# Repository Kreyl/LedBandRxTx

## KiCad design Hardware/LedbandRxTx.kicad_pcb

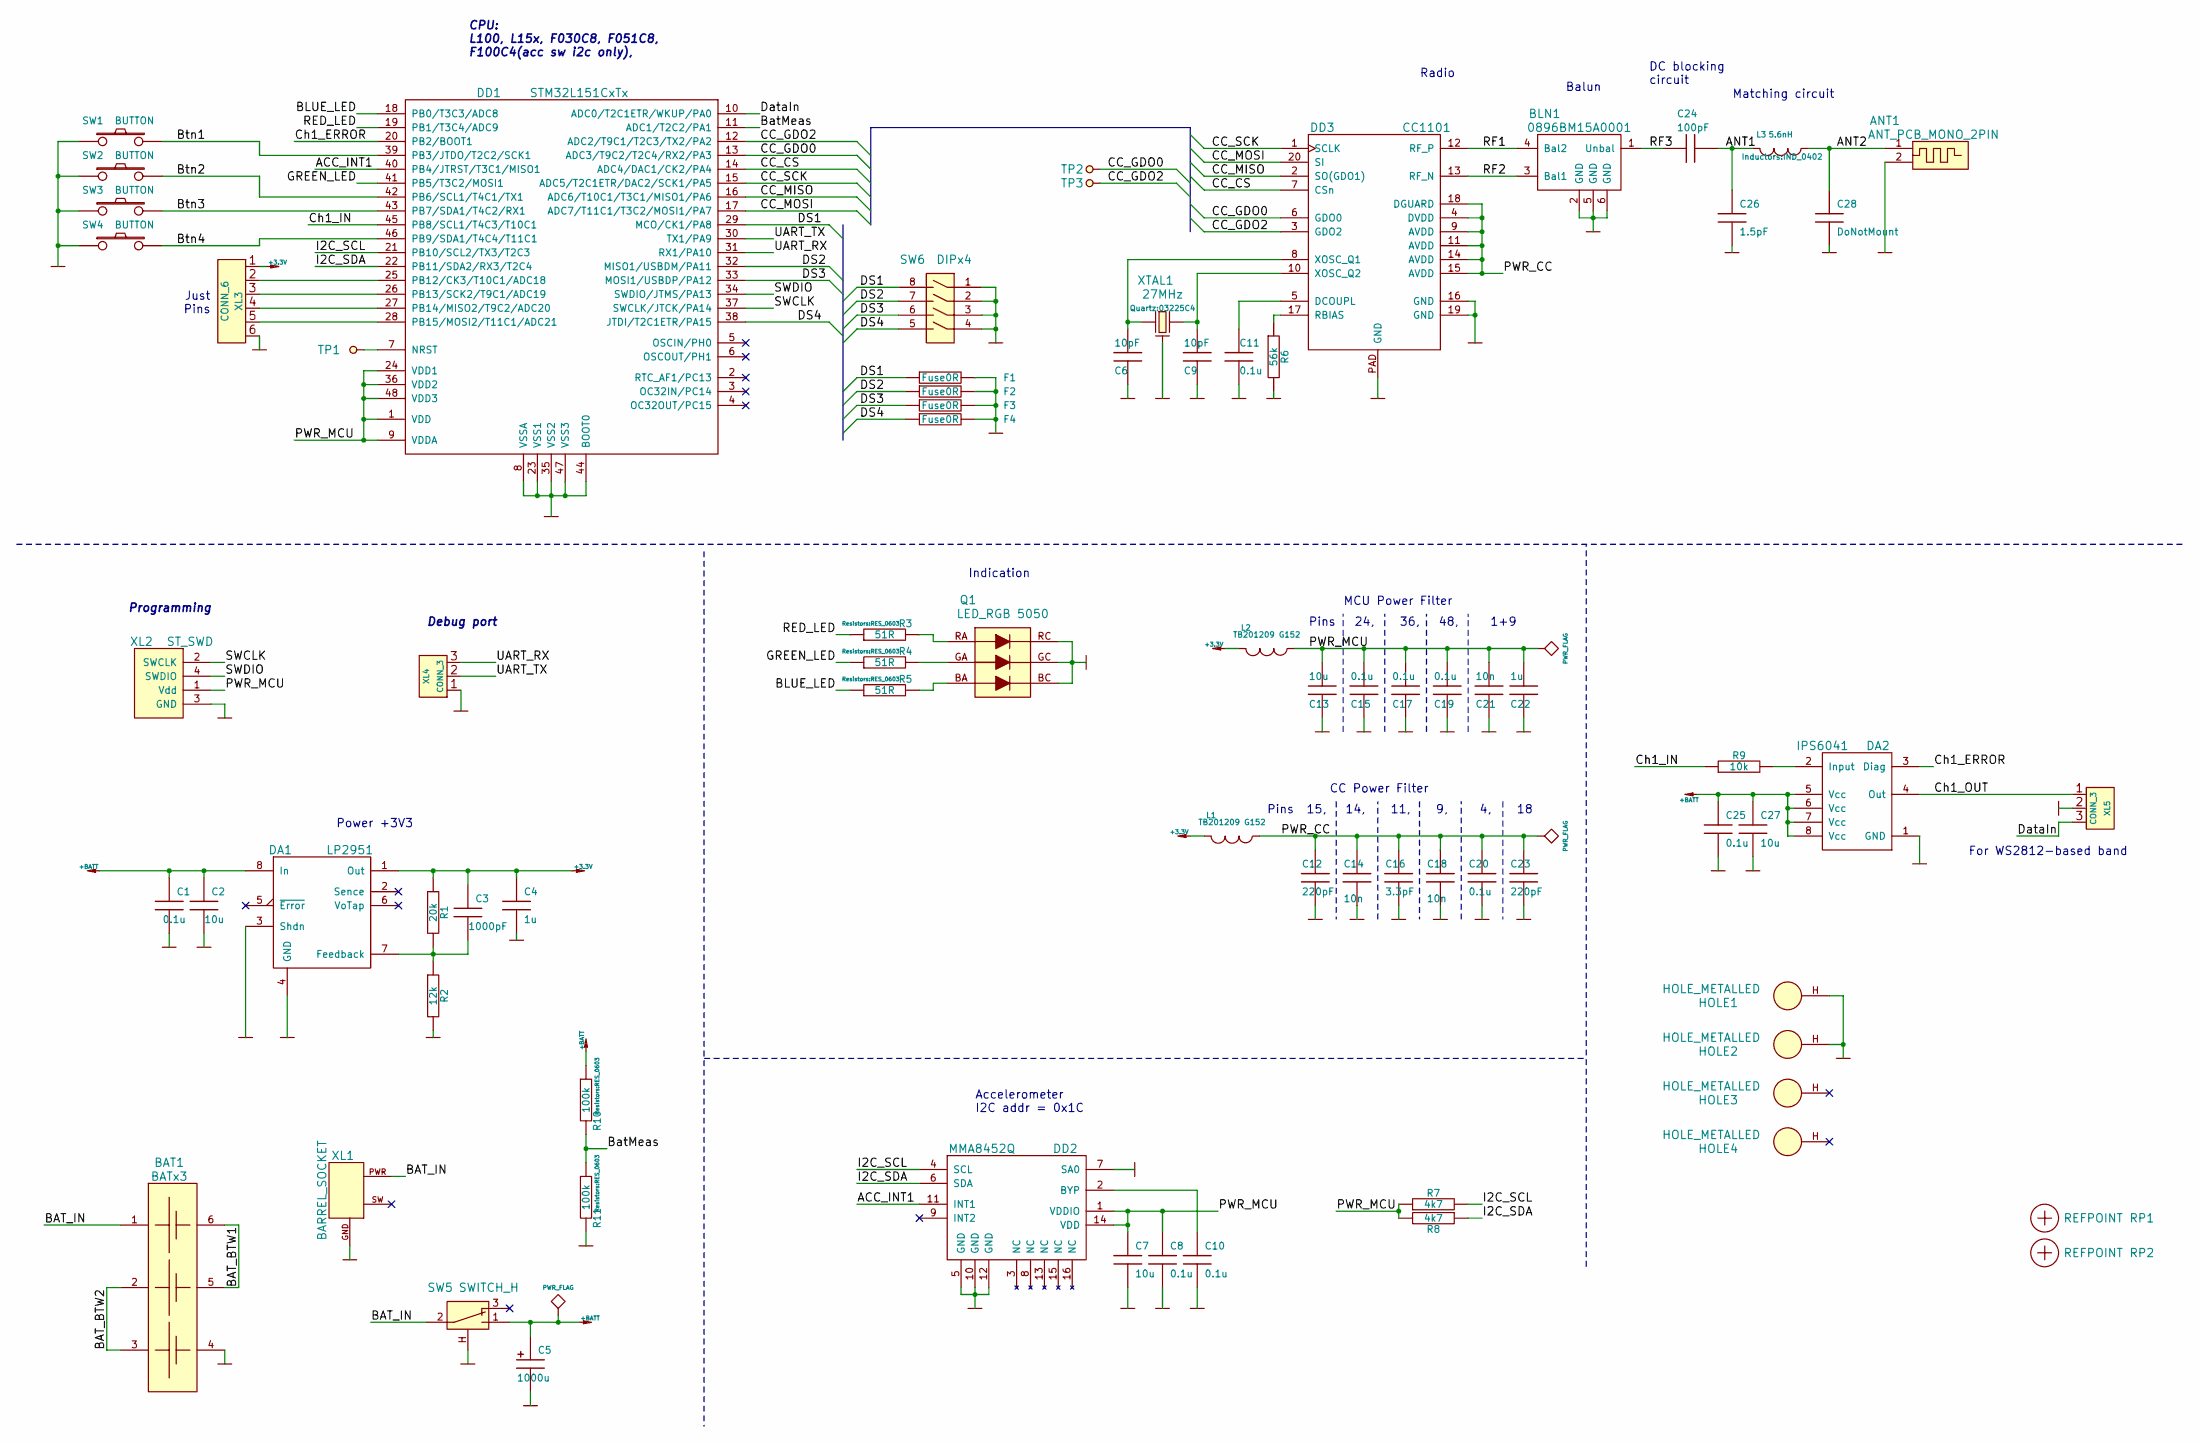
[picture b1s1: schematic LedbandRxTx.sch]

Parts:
ANT1: ANT_PCB_MONO_2PIN; ANT_INVF_LEDBANDRXTX
BAT1: BATx3; 18650x3
BLN1: 0896BM15A0001; BALUN_JOHANSON868
C1, C8, C10, C11, C15, C17, C19, C20, C25: 0.1u; CAP_0603
C2, C7, C13, C27: 10u; CAP_0805
C3: 1000pF; CAP_0603
C4, C22: 1u; CAP_0603
C5: 1000u; CAP_10xxR
C6, C9: 10pF; CAP_0603
C12, C23: 220pF; CAP_0603
C14, C18, C21: 10n; CAP_0603
C16: 3.3pF; CAP_0603
C24: 100pF; CAP_0402
C26: 1.5pF; CAP_0402
C28: DoNotMount; CAP_0402
DA1: LP2951; SO8
DA2: IPS6041; SO8HEATSINK
DD1: STM32L151CxTx; LQFP48
DD2: MMA8452Q; QFN16_5_3
DD3: CC1101; QFN20
F1, F2, F3, F4: Fuse0R; RES_0603_SOLDERFUSE
HOLE1, HOLE2, HOLE3, HOLE4: HOLE_METALLED; Hole3_5_out6mm
L1, L2: TB201209 G152; IND_0805
L3: 5.6nH; IND_0402
Q1: LED_RGB 5050; LED_5050
R1: 20k; RES_0603
R2: 12k; RES_0603
R3, R4, R5: 51R; RES_0603
R6: 56k; RES_0603
R7, R8: 4k7; RES_0603
R9: 10k; RES_0603
R10, R11: 100k; RES_0603
RP1, RP2: REFPOINT; REF_POINT_1MM
SW1, SW2, SW3, SW4: BUTTON; BTN_SWT9
SW5: SWITCH_H; SW_SS9
SW6: DIPx4; DIP_SMD_X4
TP1, TP2, TP3: TESTPOINT; TESTPOINT_1MM
XL1: BARREL_SOCKET; Barrel
XL2: ST_SWD; PLS-4
XL3: CONN_6; PLS-6
XL4: CONN_3; PLS-3
XL5: CONN_3; TermiBlockHeader_508_x3_R
XTAL1: 27MHz; 03225C4

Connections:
+3.3V: C3.1, C4.1, DA1.1 (Out), L1.2, L2.2, R1.1, XL3.1
+BATT: C1.1, C2.1, C5.1, C25.1, C27.1, DA1.8 (In), DA2.5 (Vcc), DA2.6 (Vcc), DA2.7 (Vcc), DA2.8 (Vcc), R10.1, SW5.1
/ACC_INT1: DD1.40 (PB4/JTRST/T3C1/MISO1), DD2.11 (INT1)
/ANT1: C24.1, C26.1, L3.2
/ANT2: ANT1.1, C28.1, L3.1
/BAT_BTW1: BAT1.5 (C2), BAT1.6 (C1)
/BAT_BTW2: BAT1.2 (A2), BAT1.3 (A3)
/BAT_IN: BAT1.1 (A1), SW5.2, XL1.PWR
/BLUE_LED: DD1.18 (PB0/T3C3/ADC8), R5.1
/BatMeas: DD1.11 (ADC1/T2C2/PA1), R10.2, R11.1
/Btn1: DD1.39 (PB3/JTDO/T2C2/SCK1), SW1.2
/Btn2: DD1.42 (PB6/SCL1/T4C1/TX1), SW2.2
/Btn3: DD1.43 (PB7/SDA1/T4C2/RX1), SW3.2
/Btn4: DD1.46 (PB9/SDA1/T4C4/T11C1), SW4.2
/CC_CS: DD1.14 (ADC4/DAC1/CK2/PA4), DD3.7 (CSn)
/CC_GDO0: DD1.13 (ADC3/T9C2/T2C4/RX2/PA3), DD3.6 (GDO0), TP2.1
/CC_GDO2: DD1.12 (ADC2/T9C1/T2C3/TX2/PA2), DD3.3 (GDO2), TP3.1
/CC_MISO: DD1.16 (ADC6/T10C1/T3C1/MISO1/PA6), DD3.2 (SO(GDO1))
/CC_MOSI: DD1.17 (ADC7/T11C1/T3C2/MOSI1/PA7), DD3.20 (SI)
/CC_SCK: DD1.15 (ADC5/T2C1ETR/DAC2/SCK1/PA5), DD3.1 (SCLK)
/Ch1_ERROR: DA2.3 (Diag), DD1.20 (PB2/BOOT1)
/Ch1_IN: DD1.45 (PB8/SCL1/T4C3/T10C1), R9.1
/Ch1_OUT: DA2.4 (Out), XL5.1
/DS1: DD1.29 (MCO/CK1/PA8), F1.1, SW6.8
/DS2: DD1.32 (MISO1/USBDM/PA11), F2.1, SW6.7
/DS3: DD1.33 (MOSI1/USBDP/PA12), F3.1, SW6.6
/DS4: DD1.38 (JTDI/T2C1ETR/PA15), F4.1, SW6.5
/DataIn: DD1.10 (ADC0/T2C1ETR/WKUP/PA0), XL5.3
/GREEN_LED: DD1.41 (PB5/T3C2/MOSI1), R4.1
/I2C_SCL: DD1.21 (PB10/SCL2/TX3/T2C3), DD2.4 (SCL), R7.2
/I2C_SDA: DD1.22 (PB11/SDA2/RX3/T2C4), DD2.6 (SDA), R8.1
/PWR_CC: C12.1, C14.1, C16.1, C18.1, C20.1, C23.1, DD3.4 (DVDD), DD3.9 (AVDD), DD3.11 (AVDD), DD3.14 (AVDD), DD3.15 (AVDD), DD3.18 (DGUARD), L1.1
/PWR_MCU: C7.1, C8.1, C13.1, C15.1, C17.1, C19.1, C21.1, C22.1, DD1.1 (VDD), DD1.9 (VDDA), DD1.24 (VDD1), DD1.36 (VDD2), DD1.48 (VDD3), DD2.1 (VDDIO), DD2.14 (VDD), L2.1, R7.1, R8.2, XL2.1 (Vdd)
/RED_LED: DD1.19 (PB1/T3C4/ADC9), R3.1
/RF1: BLN1.4 (Bal2), DD3.12 (RF_P)
/RF2: BLN1.3 (Bal1), DD3.13 (RF_N)
/RF3: BLN1.1 (Unbal), C24.2
/SWCLK: DD1.37 (SWCLK/JTCK/PA14), XL2.2 (SWCLK)
/SWDIO: DD1.34 (SWDIO/JTMS/PA13), XL2.4 (SWDIO)
/UART_RX: DD1.31 (RX1/PA10), XL4.3
/UART_TX: DD1.30 (TX1/PA9), XL4.2 (PM)
GND: ANT1.2, BAT1.4 (C3), BLN1.2 (GND), BLN1.5 (GND), BLN1.6 (GND), C1.2, C2.2, C4.2, C5.2, C6.2, C7.2, C8.2, C9.2, C10.2, C11.2, C12.2, C13.2, C14.2, C15.2, C16.2, C17.2, C18.2, C19.2, C20.2, C21.2, C22.2, C23.2, C25.2, C26.2, C27.2, C28.2, DA1.3 (Shdn), DA1.4 (GND), DA2.1 (GND), DD1.8 (VSSA), DD1.23 (VSS1), DD1.35 (VSS2), DD1.44 (BOOT0), DD1.47 (VSS3), DD2.5 (GND), DD2.7 (SA0), DD2.10 (GND), DD2.12 (GND), DD3.16 (GND), DD3.19 (GND), DD3.PAD (GND), F1.2, F2.2, F3.2, F4.2, HOLE1.H, HOLE2.H, Q1.BC (B), Q1.GC (G), Q1.RC, R2.2, R6.2, R11.2, SW1.1, SW2.1, SW3.1, SW4.1, SW5.H, SW6.1, SW6.2, SW6.3, SW6.4, XL1.GND, XL2.3 (GND), XL3.6, XL4.1, XL5.2 (PM), XTAL1.H
unnamed: C3.2, DA1.7 (Feedback), R1.2, R2.1
unnamed: C6.1, DD3.8 (XOSC_Q1), XTAL1.1
unnamed: C9.1, DD3.10 (XOSC_Q2), XTAL1.2
unnamed: C10.1, DD2.2 (BYP)
unnamed: C11.1, DD3.5 (DCOUPL)
unnamed: DA2.2 (Input), R9.2
unnamed: DD1.7 (NRST), TP1.1
unnamed: DD1.25 (PB12/CK3/T10C1/ADC18), XL3.2
unnamed: DD1.26 (PB13/SCK2/T9C1/ADC19), XL3.3
unnamed: DD1.27 (PB14/MISO2/T9C2/ADC20), XL3.4
unnamed: DD1.28 (PB15/MOSI2/T11C1/ADC21), XL3.5
unnamed: DD3.17 (RBIAS), R6.1
unnamed: Q1.BA, R5.2
unnamed: Q1.GA, R4.2
unnamed: Q1.RA, R3.2

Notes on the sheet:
Radio
Matching circuit
Debug port
Programming
CPU: L100, L15x, F030C8, F051C8, F100C4(acc sw i2c only),
Indication
Just Pins
Power +3V3
Accelerometer I2C addr = 0x1C
Balun
DC blocking circuit
MCU Power Filter
Pins 24, 36, 48, 1+9
CC Power Filter
Pins 15, 14, 11, 9, 4, 18
For WS2812-based band

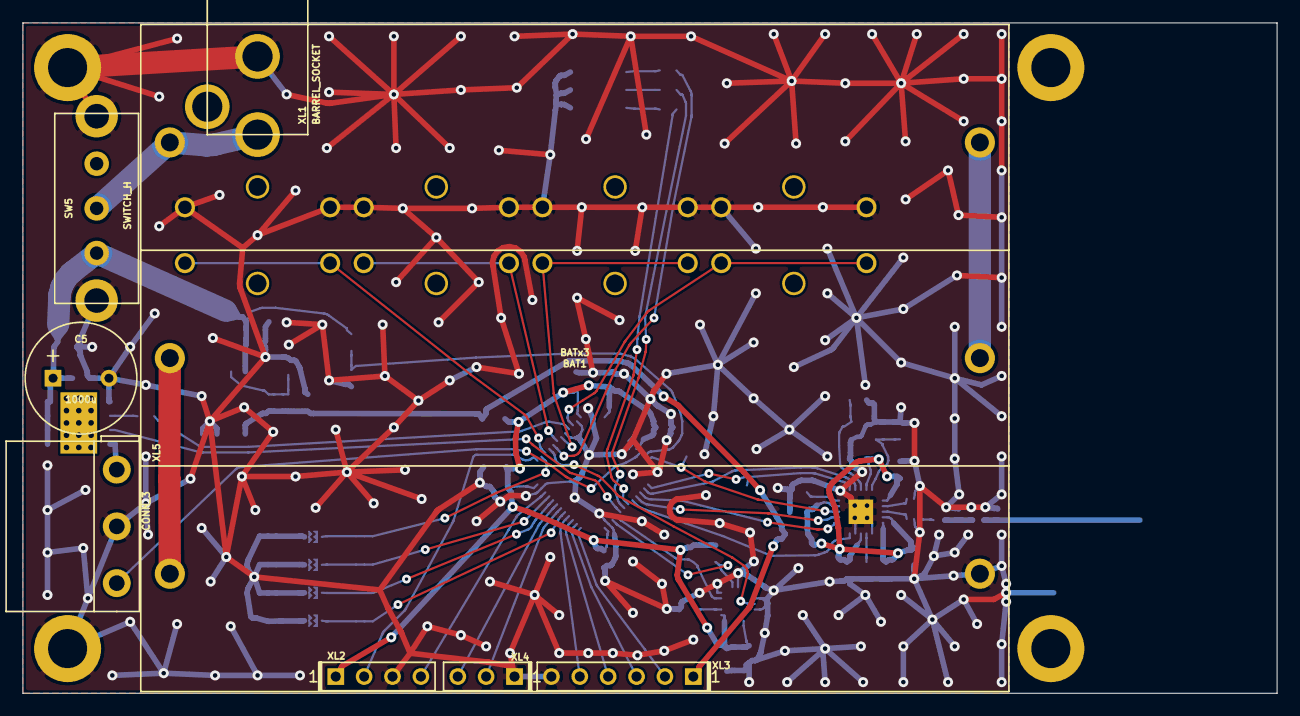
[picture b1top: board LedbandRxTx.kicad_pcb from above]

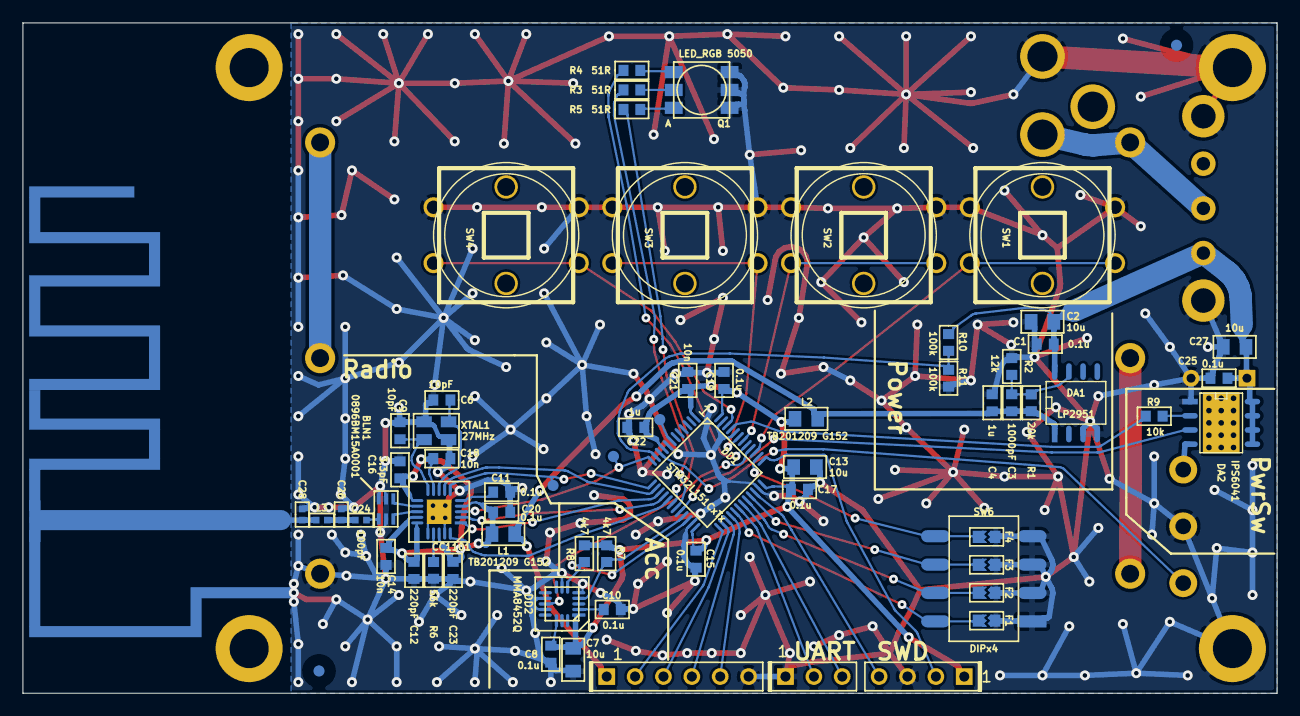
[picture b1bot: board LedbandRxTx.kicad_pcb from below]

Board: 2 copper layers, 112.2 x 60.0 mm, 76 parts (64 on the bottom side), 57 nets.

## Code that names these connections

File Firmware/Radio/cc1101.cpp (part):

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static const PinIrq_t IGdo0(CC_GDO0_IRQ);
static thread_reference_t ThdRef;

#define CsHi()  PinSetHi(CC_GPIO, CC_CS)
#define CsLo()  PinSetLo(CC_GPIO, CC_CS)

uint8_t cc1101_t::Init() {
    // ==== GPIO ====
    PinSetupOut      (CC_GPIO, CC_CS,   omPushPull);
    PinSetupAlterFunc(CC_GPIO, CC_SCK,  omPushPull, pudNone, CC_SPI_AF);
    PinSetupAlterFunc(CC_GPIO, CC_MISO, omPushPull, pudNone, CC_SPI_AF);
    PinSetupAlterFunc(CC_GPIO, CC_MOSI, omPushPull, pudNone, CC_SPI_AF);
    IGdo0.Init(ttFalling);
    //PinSetupAnalog   (CC_GPIO, CC_GDO2);    // GDO2 not used
    CsHi();
    // ==== SPI ====
    // MSB first, master, ClkLowIdle, FirstEdge, Baudrate no more than 6.5MHz
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
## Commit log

2015-08-29 + Sch Components placement started
2015-08-30 PCB routing started. Antenna under construction
2015-08-30 PCB routed, antenna still in progress
2015-08-31 + PCB is ready, sent to production
2015-09-06 + First firmware commit
2015-09-06 + LED + Buttons + RX/TX switch
2015-09-06 + Radio works + Radio matched
2015-09-07 * Quartz capacitors changed * Channel moved to 0 (868) from 180 (944)
2015-09-08 + Cases * Btns order changed
2015-09-08 + gitignore
2016-07-25 + Led ok
2016-09-28 Release
2016-09-28 Btns and blinks
2016-09-28 + TX and RX works
2017-08-31 Switch to new os and evt system
2017-08-31 + btns
